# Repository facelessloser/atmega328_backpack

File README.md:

# atmega328_backpack
programmer/serial backpack for the atmega328 chip when bread boarding

HackaDay.io project log - https://hackaday.io/project/8474-atmega328-programmerftdi-backpack-board

Blog post - https://facelesstech.wordpress.com/2015/12/09/atmega328-backpack/

Youtube video - https://www.youtube.com/watch?v=iEx4xWTJ0U4

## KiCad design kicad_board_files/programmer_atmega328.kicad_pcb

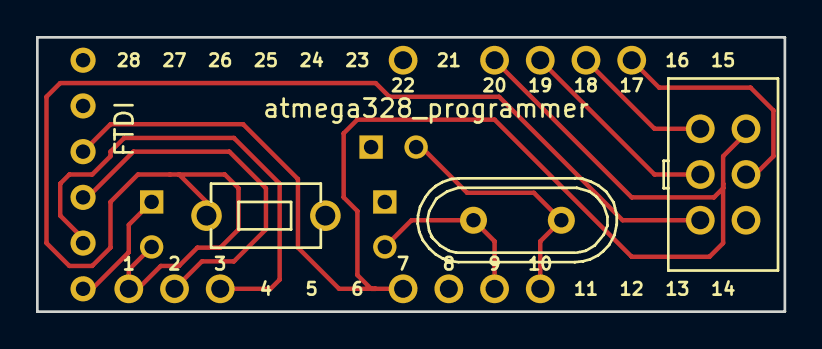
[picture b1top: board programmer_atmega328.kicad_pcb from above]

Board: 2 copper layers, 41.5 x 15.2 mm, 9 parts (0 on the bottom side), 11 nets.

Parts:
C1, C2, C3: C; C_Disc_D3_P2.5
CON1: AVR-ISP-6; IDC_6pin_small_custom
FTDI1: FTDI
SW1: SW_PUSH; button_slim_custom
U1: atmega328_programmer
VAL: OSH_final_silks_back
Y1: Crystal; Crystal_HC49-U_Vertical

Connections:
GND: C1.1, C2.1, CON1.6, FTDI1.1, SW1.2, U1.8
unnamed: C1.2, U1.10, Y1.1
unnamed: C2.2, U1.9, Y1.2
unnamed: C3.1, FTDI1.6
unnamed: C3.2, CON1.5, SW1.1, U1.1
unnamed: CON1.1, U1.3
unnamed: CON1.3, U1.2
unnamed: CON1.4, U1.4
unnamed: FTDI1.4, U1.5
unnamed: FTDI1.5, U1.6
VCC: CON1.2, FTDI1.3, U1.7

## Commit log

2015-11-17 kicad gerber files for atmega328 backpack
2015-12-01 fixed pin 9 and 10 drill holes and made them all bigger
2015-12-01 added HackaDay.io project log link
2015-12-09 Added links to blog and youtube video
2016-09-24 Added board files
